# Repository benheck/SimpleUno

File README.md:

# SimpleUno
An extremely bare-bones ATMEGA328P PDIP-28 Arduino Uno compatible dev board.

INSTRUCTIONS:

Use existing socketed Arduino Uno dev board to flash bootloader/fuses onto a PDIP-28 ATMEG328P

Place programmed IC into this dev board either directly soldered or with a socket.

Attach 6 pin FTDI cable, breakout board or such compatible device.

In Arduino IDE select the FTDI's port and set the board as Arduino Uno.

Program away!

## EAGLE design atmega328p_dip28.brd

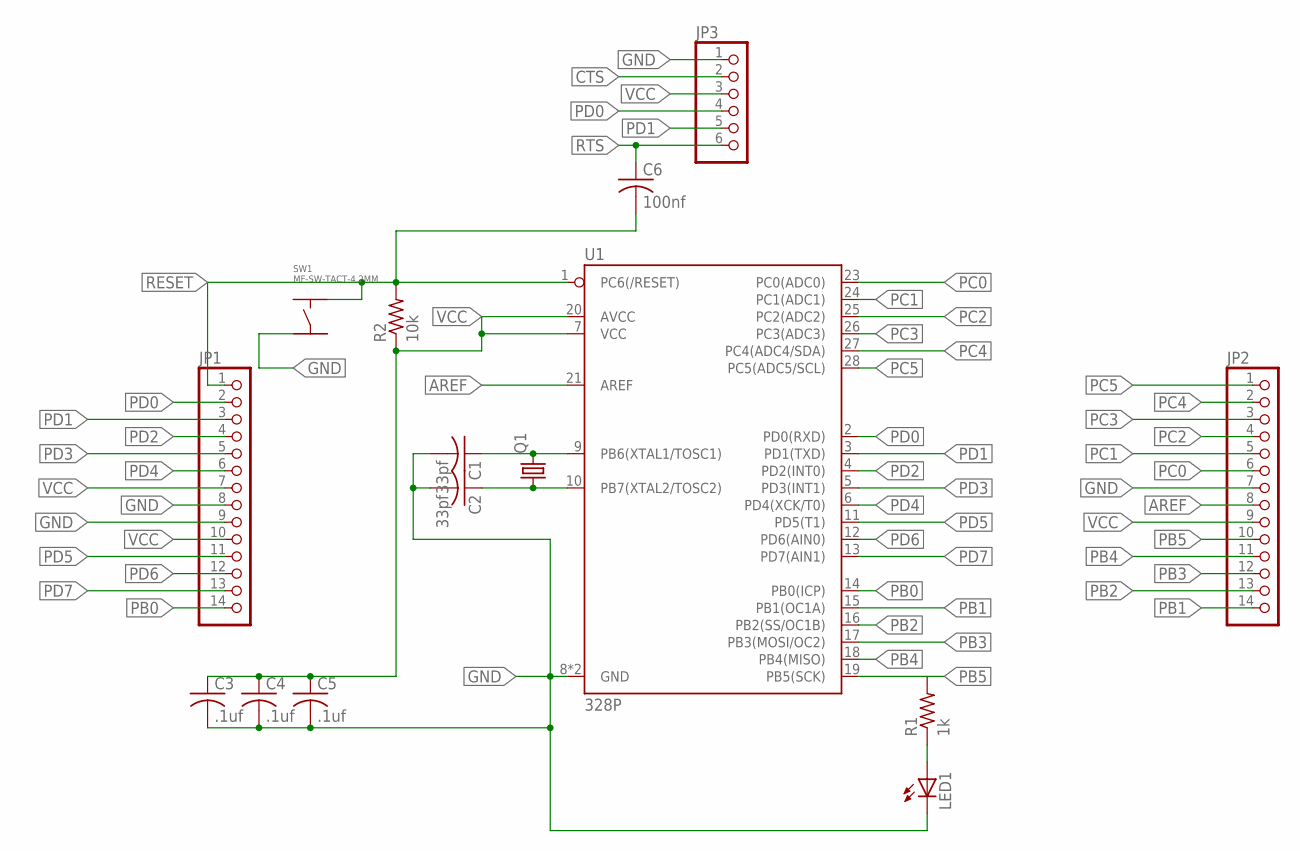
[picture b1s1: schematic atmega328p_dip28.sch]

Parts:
C1, C2: 33pf; C0603K
C3, C4, C5: .1uf; C0603
C6: 100nf; C0603
JP1, JP2: PINHD-1X14-CB; 1X14-CB
JP3: PINHD-1X6; 1X06
LED1: LEDCHIP-LED0805; CHIP-LED0805
Q1: CRYSTALCTS406; CTS406
R1: 1k; R0603
R2: 10k; R0603
SW1: MF-SW-TACT-4.2MM; MF_SWITCHES_TACT4.2MM
U1: 328P; DIP28

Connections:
AREF: JP2.8, U1.21 (AREF)
CTS: JP3.2
GND: C1.2, C2.2, C3.2, C4.2, C5.2, JP1.8, JP1.9, JP2.7, JP3.1, LED1.C, SW1.P$3, U1.8 (GND), U1.22 (GND)
unnamed: C1.1, Q1.3 (2), U1.9 (PB6(XTAL1/TOSC1))
unnamed: C2.1, Q1.1, U1.10 (PB7(XTAL2/TOSC2))
unnamed: LED1.A, R1.1
PB0: JP1.14, U1.14 (PB0(ICP))
PB1: JP2.14, U1.15 (PB1(OC1A))
PB2: JP2.13, U1.16 (PB2(SS/OC1B))
PB3: JP2.12, U1.17 (PB3(MOSI/OC2))
PB4: JP2.11, U1.18 (PB4(MISO))
PB5: JP2.10, R1.2, U1.19 (PB5(SCK))
PC0: JP2.6, U1.23 (PC0(ADC0))
PC1: JP2.5, U1.24 (PC1(ADC1))
PC2: JP2.4, U1.25 (PC2(ADC2))
PC3: JP2.3, U1.26 (PC3(ADC3))
PC4: JP2.2, U1.27 (PC4(ADC4/SDA))
PC5: JP2.1, U1.28 (PC5(ADC5/SCL))
PD0: JP1.2, JP3.4, U1.2 (PD0(RXD))
PD1: JP1.3, JP3.5, U1.3 (PD1(TXD))
PD2: JP1.4, U1.4 (PD2(INT0))
PD3: JP1.5, U1.5 (PD3(INT1))
PD4: JP1.6, U1.6 (PD4(XCK/T0))
PD5: JP1.11, U1.11 (PD5(T1))
PD6: JP1.12, U1.12 (PD6(AIN0))
PD7: JP1.13, U1.13 (PD7(AIN1))
RESET: C6.2, JP1.1, R2.2, SW1.P$2, U1.1 (PC6(/RESET))
RTS: C6.1, JP3.6
VCC: C3.1, C4.1, C5.1, JP1.7, JP1.10, JP2.9, JP3.3, R2.1, U1.7 (VCC), U1.20 (AVCC)

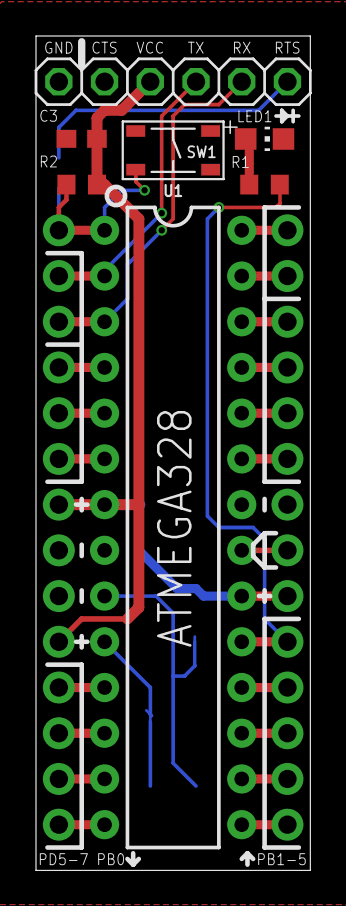
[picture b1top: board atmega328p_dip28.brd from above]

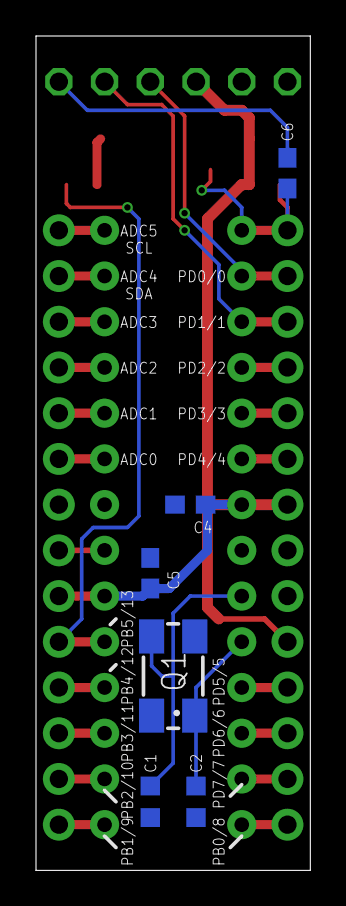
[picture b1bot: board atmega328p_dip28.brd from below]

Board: 2 copper layers, 15.2 x 46.4 mm, 15 parts (6 on the bottom side), 28 nets.

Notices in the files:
parts and their libraries:
SparkFun-IC-Microcontroller: Licensing: Creative Commons ShareAlike 4.0 International - https://creativecommons.org/licenses/by-sa/4.0
